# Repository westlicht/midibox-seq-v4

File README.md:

# midibox-seq-v4

This repository contains some documentation and data created during the build process of a MIDIBox SEQ V4. Please note that I'm **not** the original author of the project. The original project is hosted at http://ucapps.de

## MIDIbox PCBs

I ordered the PCBs from http://midiboxshop.bigcartel.com

Here is the list:

- 1x [CORE STMF32 BOARD](http://midiboxshop.bigcartel.com/product/core-stm32f4-board)
- 2x [MIDI I/O MODULE BOARD](http://midiboxshop.bigcartel.com/product/midi-i-o-module-board)
- 1x [DOUT MODULE BOARD](http://midiboxshop.bigcartel.com/product/dout-module-board)
- 1x [AOUT_NG BOARD](http://midiboxshop.bigcartel.com/product/aout_ng-module-board)
- 1x [SEQ CS BOARD](http://midiboxshop.bigcartel.com/product/seq-cs-board)

## Parts

I ordered the parts from [TME](http://www.tme.eu/en), [Reichelt](http://www.reichelt.com/), [DigiKey](http://www.digikey.com) and [Mouser](http://www.mouser.com). Sourcing the parts is a little painful. In addition, for some parts there are a few (or many) options. The following are a few notes on the parts I've chosen for the build:

- ALPS [Reichelt](https://www.reichelt.com/Drehimpulsgeber/STEC12E08/3/index.html?&ACTION=3&LA=5011&GROUP=B29&GROUPID=3714&ARTICLE=73923&OFFSET=1000&SORT=artnr)
TODO

## Custom PCB

As I wanted to have nice backpanel as well as Ethernet support, I designed a PCB with the following additional features:

- Ethernet via SPI (based on http://ucapps.de/mbhp_eth.html)
- SD card socket
- USB connector
- +/- 12V DC/DC converter for the AOUT power supply

The PCB was designed in [KiCad](http://kicad.org/) and produced by [OSH Park](https://oshpark.com/). The PCB is available [here](https://oshpark.com/shared_projects/DuxxcHS7). Feel free to order your own!

Here is the bill of materials:

| Part | Description | Supplier |
| --- | --- | --- |
| C1, C4, C5, C6, C8, C9, C10, C11, C14, C15 | Ceramic Capacitor 100 nF |
| C2, C3 | Ceramic Capacitor 18 pF |
| C7 | Tantal Capacitor 10 uF |
| C12, C16 | Polarized Capacitor 47 uF |
| C13 | Polarized Capacitor 100 uF |
| R1 | Resistor 2.32 kOhm |
| R2, R3, R4, R5 | Resistor 49.9 Ohm |
| R6, R7 | Resistor 220 Ohm |
| L1 | Ferrit Bead 10 uH | [Reichelt](https://www.reichelt.com/Filter/BEAD-10-60/3/index.html?&ACTION=3&LA=5011&GROUP=B43&GROUPID=3175&ARTICLE=105527&OFFSET=1000&SORT=artnr) |
| Y1 | Crystal 25 MHz | [Reichelt](https://www.reichelt.com/Quarze/25-0000-HC49U-S/3/index.html?&ACTION=3&LA=5011&GROUP=B41&GROUPID=3173&ARTICLE=58657&OFFSET=1000&SORT=artnr) |
| IC1 | ENC28J60-I/SP DIP | [DigiKey](http://www.digikey.ch/product-detail/de/ENC28J60-I%2FSP/ENC28J60-I%2FSP-ND/1680061) |
| P1 | USB B connector | TODO |
| U1 | 3M SD-RSMT-2-MQ | [Mouser](http://www.mouser.ch/ProductDetail/3M-Electronic-Solutions-Division/SD-RSMT-2-MQ/?qs=sGAEpiMZZMufgI%252bQGy4rlDprx2TSk7jDVrUYDCI8Alc%3d) |
| U2 | NMH0512SC ([datasheet](http://www.farnell.com/datasheets/1790401.pdf)) | [Reichelt](https://www.reichelt.com/Wandler-Module-DC-DC/NMH0512SC/3/index.html?&ACTION=3&LA=5011&GROUP=P853&GROUPID=4956&ARTICLE=140676&OFFSET=1000&SORT=artnr)
| U3 | Pulse J0026D21E | [Mouser](http://www.mouser.ch/search/ProductDetail.aspx?r=673-J0026D21E) |

## Frontpanel / Case

The frontpanel is based on the [Wilba frontpanel](http://www.midibox.org/dokuwiki/doku.php?id=wilba_mb_seq). I only adjusted some of the drillings in addition to moving things around slightly to make sure everything fits within the case. The backpanel was designed from scratch in order to fit nicely with the MIDI I/O PCBs as well as my own PCB. In addition, a DSUB-25 connector is used for the analog bus and a few important analog outputs are available seperatly on 3.5 mm jacks. The rest of the case are just basic aluminium panels and everything is hold together by enclosure profiles. The case can be ordered from [Schaeffer AG](https://www.schaeffer-ag.de). All required files are available in the ``case`` directory.

## Notes

## Links

## Build Images

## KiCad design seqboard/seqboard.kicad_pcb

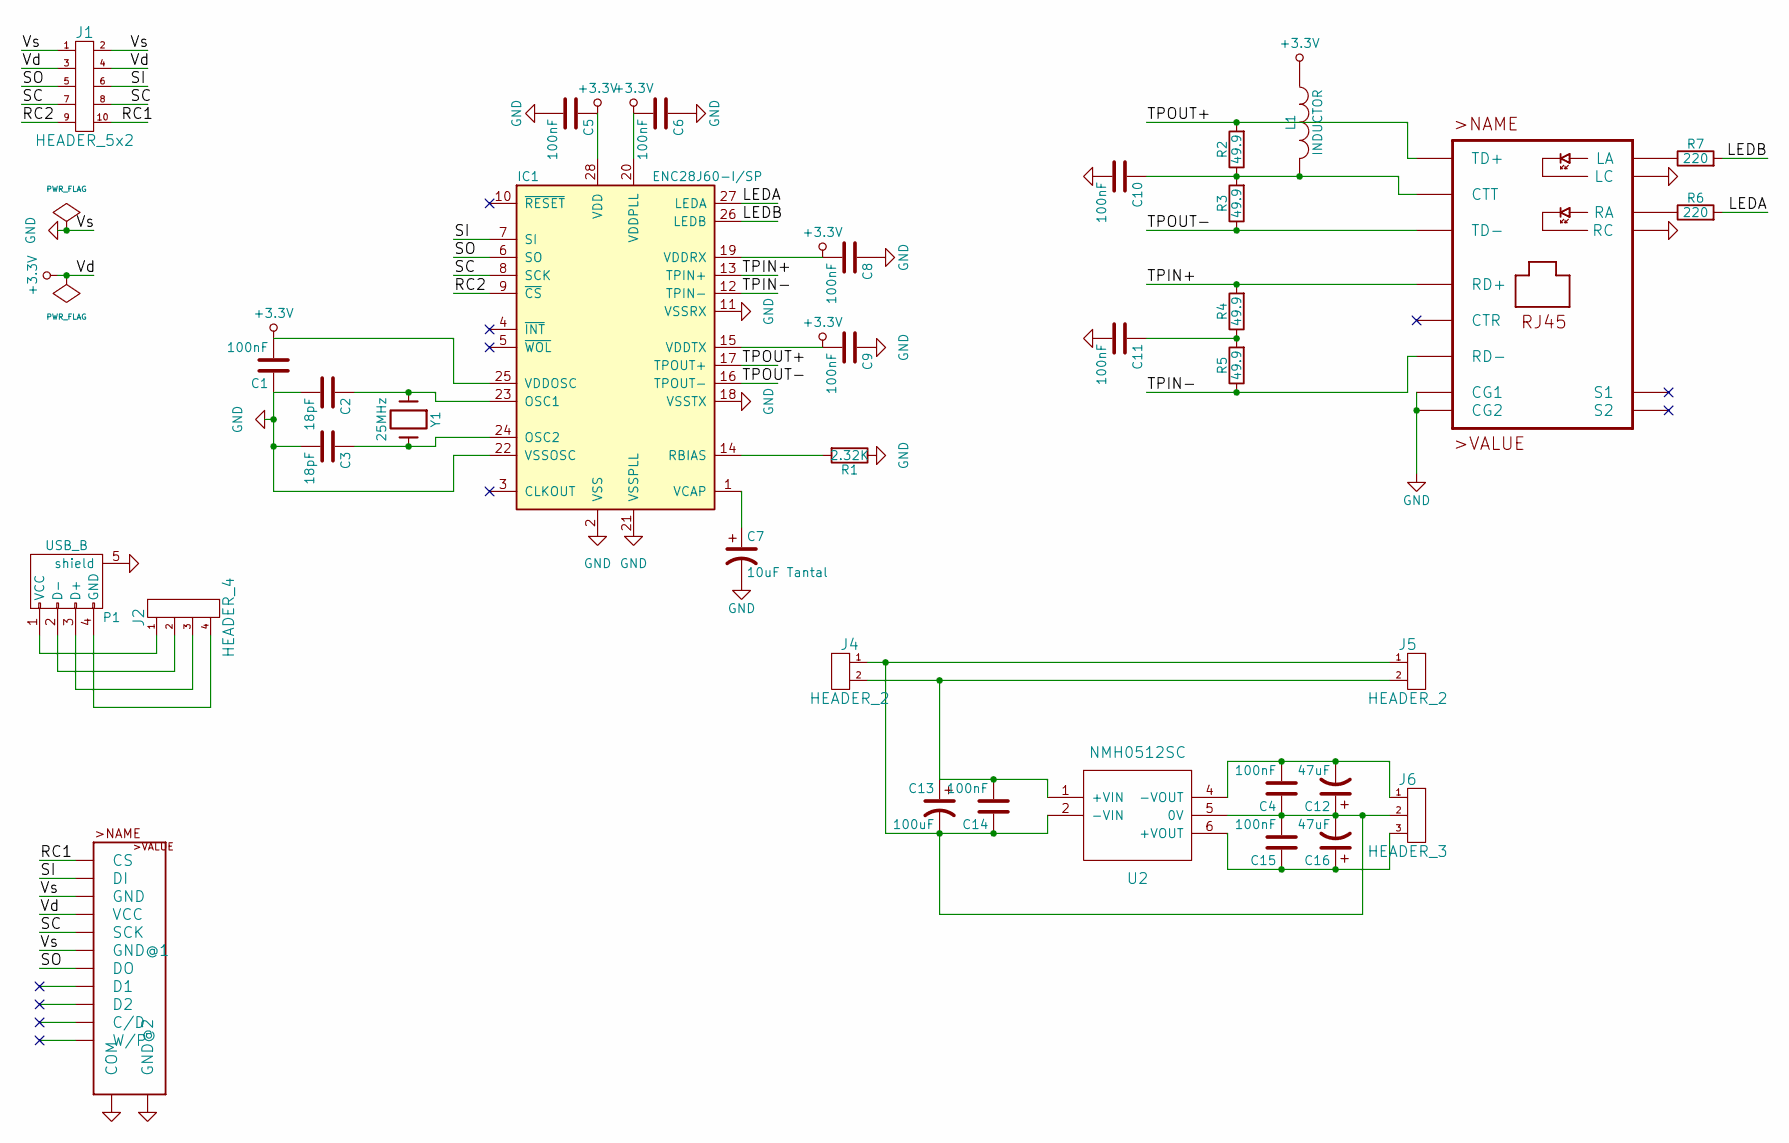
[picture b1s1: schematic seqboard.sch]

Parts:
C1, C4, C5, C6, C8, C9, C10, C11, C14, C15: 100nF; cnp_3mm_disc
C2, C3: 18pF; cnp_3mm_disc
C7: 10uF Tantal; cnp_3mm_disc
C12, C16: 47uF; C_Radial_D5_L6_P2.5
C13: 100uF; C_Radial_D5_L6_P2.5
IC1: ENC28J60-I/SP; DIP-28_W7.62mm_LongPads
J1: HEADER_5x2; IDC_Header_Straight_10pins
J2: HEADER_4; Pin_Header_Straight_1x04
J4, J5: HEADER_2; Pin_Header_Straight_1x02
J6: HEADER_3; Pin_Header_Straight_1x03
L1: INDUCTOR; R5
P1: USB_B
R1: 2.32K; Resistor_Horizontal_RM7mm
R2, R3, R4, R5: 49.9; Resistor_Horizontal_RM7mm
R6, R7: 220; Resistor_Horizontal_RM7mm
U1: SD-SOCKET-3M_SD-SOCKET-3M; SD-SOCKET-3M
U2: NMH0512SC
U3: J0026D21E_J0-A/B/F; J0-A%2fB%2fF
Y1: 25MHz; Crystal_HC49-U_Vertical

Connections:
+3.3V: C1.2, C5.1, C6.2, C8.2, C9.2, IC1.15 (VDDTX), IC1.19 (VDDRX), IC1.20 (VDDPLL), IC1.25 (VDDOSC), IC1.28 (VDD), J1.3, J1.4, L1.1, U1.4 (VCC)
/LEDA: IC1.27 (LEDA), R6.2
/LEDB: IC1.26 (LEDB), R7.2
/RC1: J1.10, U1.1 (CS)
/RC2: IC1.9 (~CS), J1.9
/SC: IC1.8 (SCK), J1.7, J1.8, U1.5 (SCK)
/SI: IC1.7 (SI), J1.6, U1.2 (DI)
/SO: IC1.6 (SO), J1.5, U1.7 (DO)
/TPIN+: IC1.13 (TPIN+), R4.2, U3.7 (RD+)
/TPIN-: IC1.12 (TPIN-), R5.1, U3.8 (RD-)
/TPOUT+: IC1.17 (TPOUT+), R2.2, U3.1 (TD+)
/TPOUT-: IC1.16 (TPOUT-), R3.1, U3.2 (TD-)
GND: C1.1, C2.2, C3.2, C5.2, C6.1, C7.2, C8.1, C9.1, C10.2, C11.2, IC1.2 (VSS), IC1.11 (VSSRX), IC1.18 (VSSTX), IC1.21 (VSSPLL), IC1.22 (VSSOSC), J1.1, J1.2, P1.5 (shield), R1.1, U1.3 (GND), U1.6 (GND@1), U1.GND@ (COM), U3.4 (CG1), U3.5 (CG2), U3.10 (LC), U3.11 (RC)
unnamed: C2.1, IC1.23 (OSC1), Y1.1
unnamed: C3.1, IC1.24 (OSC2), Y1.2
unnamed: C7.1, IC1.1 (VCAP)
unnamed: C10.1, L1.2, R2.1, R3.2, U3.3 (CTT)
unnamed: C11.1, R4.1, R5.2
unnamed: C4.1, C12.1, C13.2, C14.1, C15.2, C16.2, J4.1, J5.1, J6.2, U2.2 (-VIN), U2.5 (0V)
unnamed: C4.2, C12.2, J6.1, U2.4 (-VOUT)
unnamed: C13.1, C14.2, J4.2, J5.2, U2.1 (+VIN)
unnamed: C15.1, C16.1, J6.3, U2.6 (+VOUT)
unnamed: IC1.14 (RBIAS), R1.2
unnamed: J2.1, P1.1 (VCC)
unnamed: J2.2, P1.2 (D-)
unnamed: J2.3, P1.3 (D+)
unnamed: J2.4, P1.4 (GND)
unnamed: R6.1, U3.12 (RA)
unnamed: R7.1, U3.9 (LA)

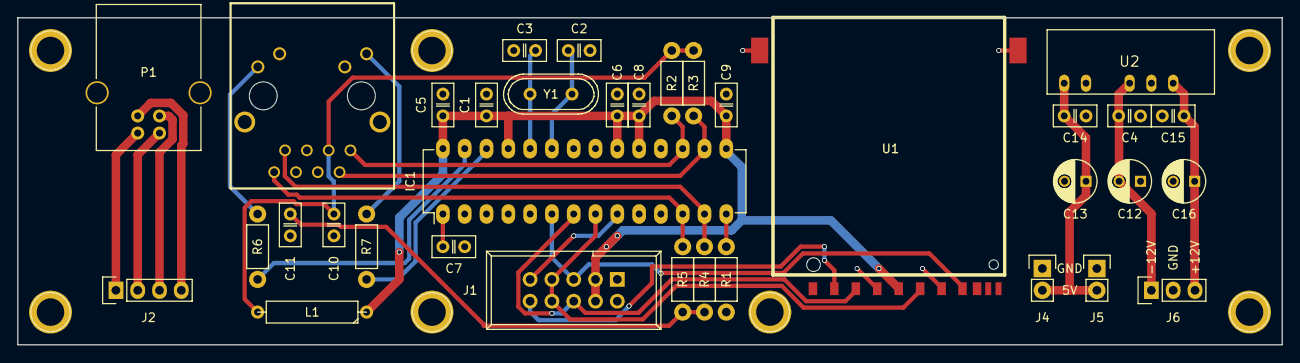
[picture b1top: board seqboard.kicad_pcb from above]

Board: 2 copper layers, 147.3 x 38.1 mm, 35 parts (0 on the bottom side), 29 nets.

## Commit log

2016-02-24 added files for case
2016-02-24 added images
2016-02-24 work on README
2016-02-24 cleanup
2018-09-29 added build images
2018-09-29 added custom pcb design files
2021-11-10 Update README.md
    https://forum.kicad.info/t/warning-avoid-all-links-to-kicad-pcb-org-use-kicad-org/31521
